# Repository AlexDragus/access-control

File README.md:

### access-control
# Access control IoT system
### 2021, Alex Dragus @ ACS, UPB
Access control Internet of Things (IoT) system using two devices with prototype PCB boards, ESP8266, relays and transistors

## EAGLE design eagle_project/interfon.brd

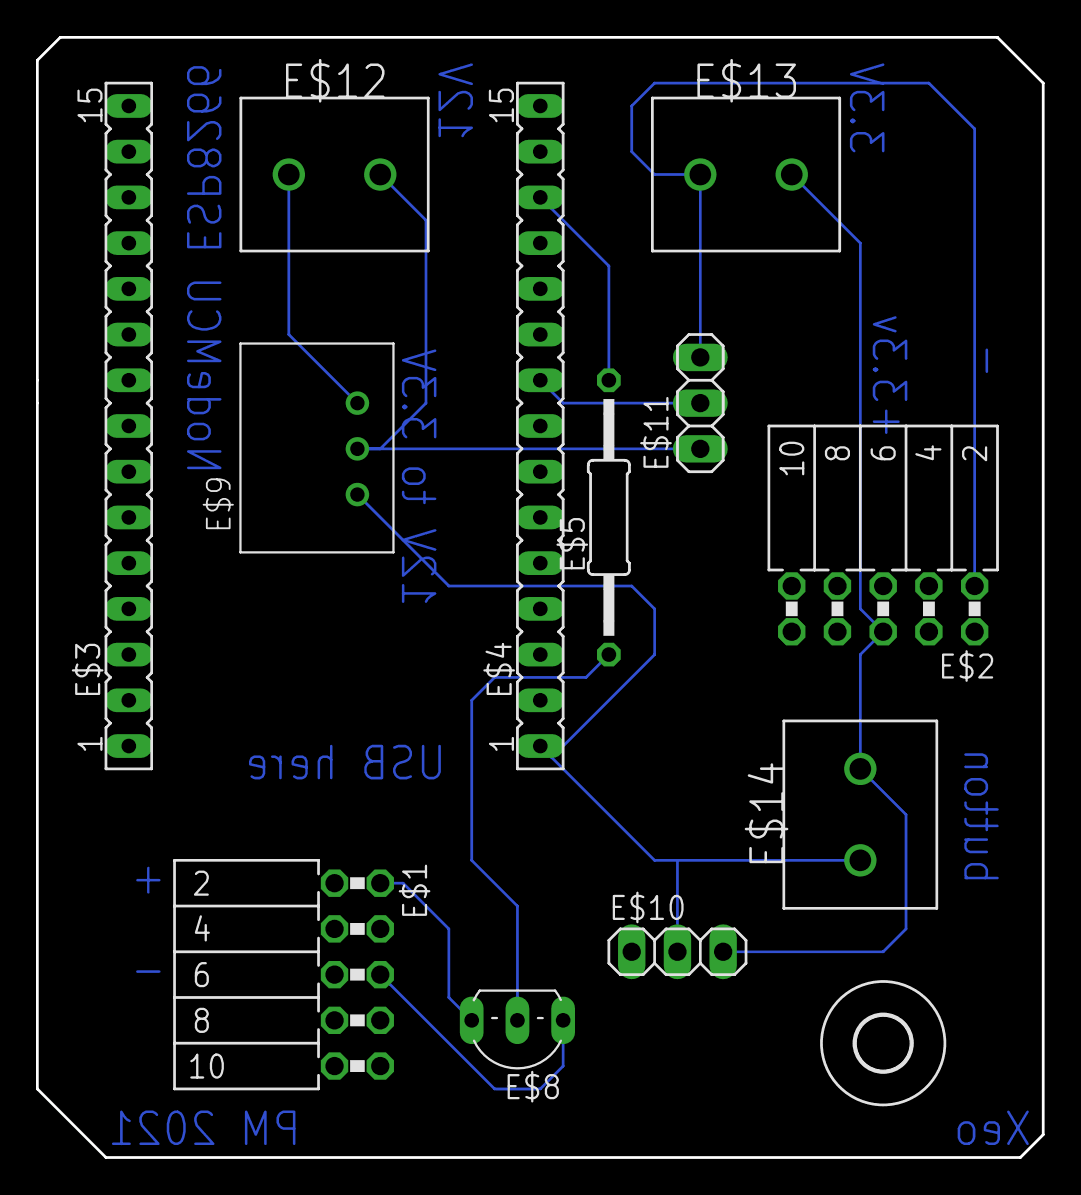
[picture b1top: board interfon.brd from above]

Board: 2 copper layers, 55.9 x 62.2 mm, 13 parts (0 on the bottom side), 8 nets.

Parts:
E$1, E$2: FE05-2W
E$3, E$4: FE15
E$5: 0207/15
E$6: 3,0
E$8: TO92-CBE
E$9: DC-DC_CONVERTER_78XX
E$10, E$11: 1X03
E$12, E$13, E$14: TERMBLK_508-2N

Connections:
S$1: E$9.VOUT, E$12.2
S$3: E$4.13, E$5.2
S$4: E$5.1, E$8.B
S$6: E$2.2, E$11.3, E$13.2
S$7: E$2.5, E$10.3, E$13.1, E$14.1
S$8: E$1.1, E$8.E
S$9: E$1.5, E$8.C
S$10: E$4.1, E$4.9, E$9.GND, E$9.VIN, E$10.2, E$11.1, E$11.2, E$12.1, E$14.2

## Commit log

2021-05-30 eagle project
2021-05-30 code

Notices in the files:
parts and their libraries:
SparkFun-IC-Power: Licensing: Creative Commons ShareAlike 4.0 International - https://creativecommons.org/licenses/by-sa/4.0
